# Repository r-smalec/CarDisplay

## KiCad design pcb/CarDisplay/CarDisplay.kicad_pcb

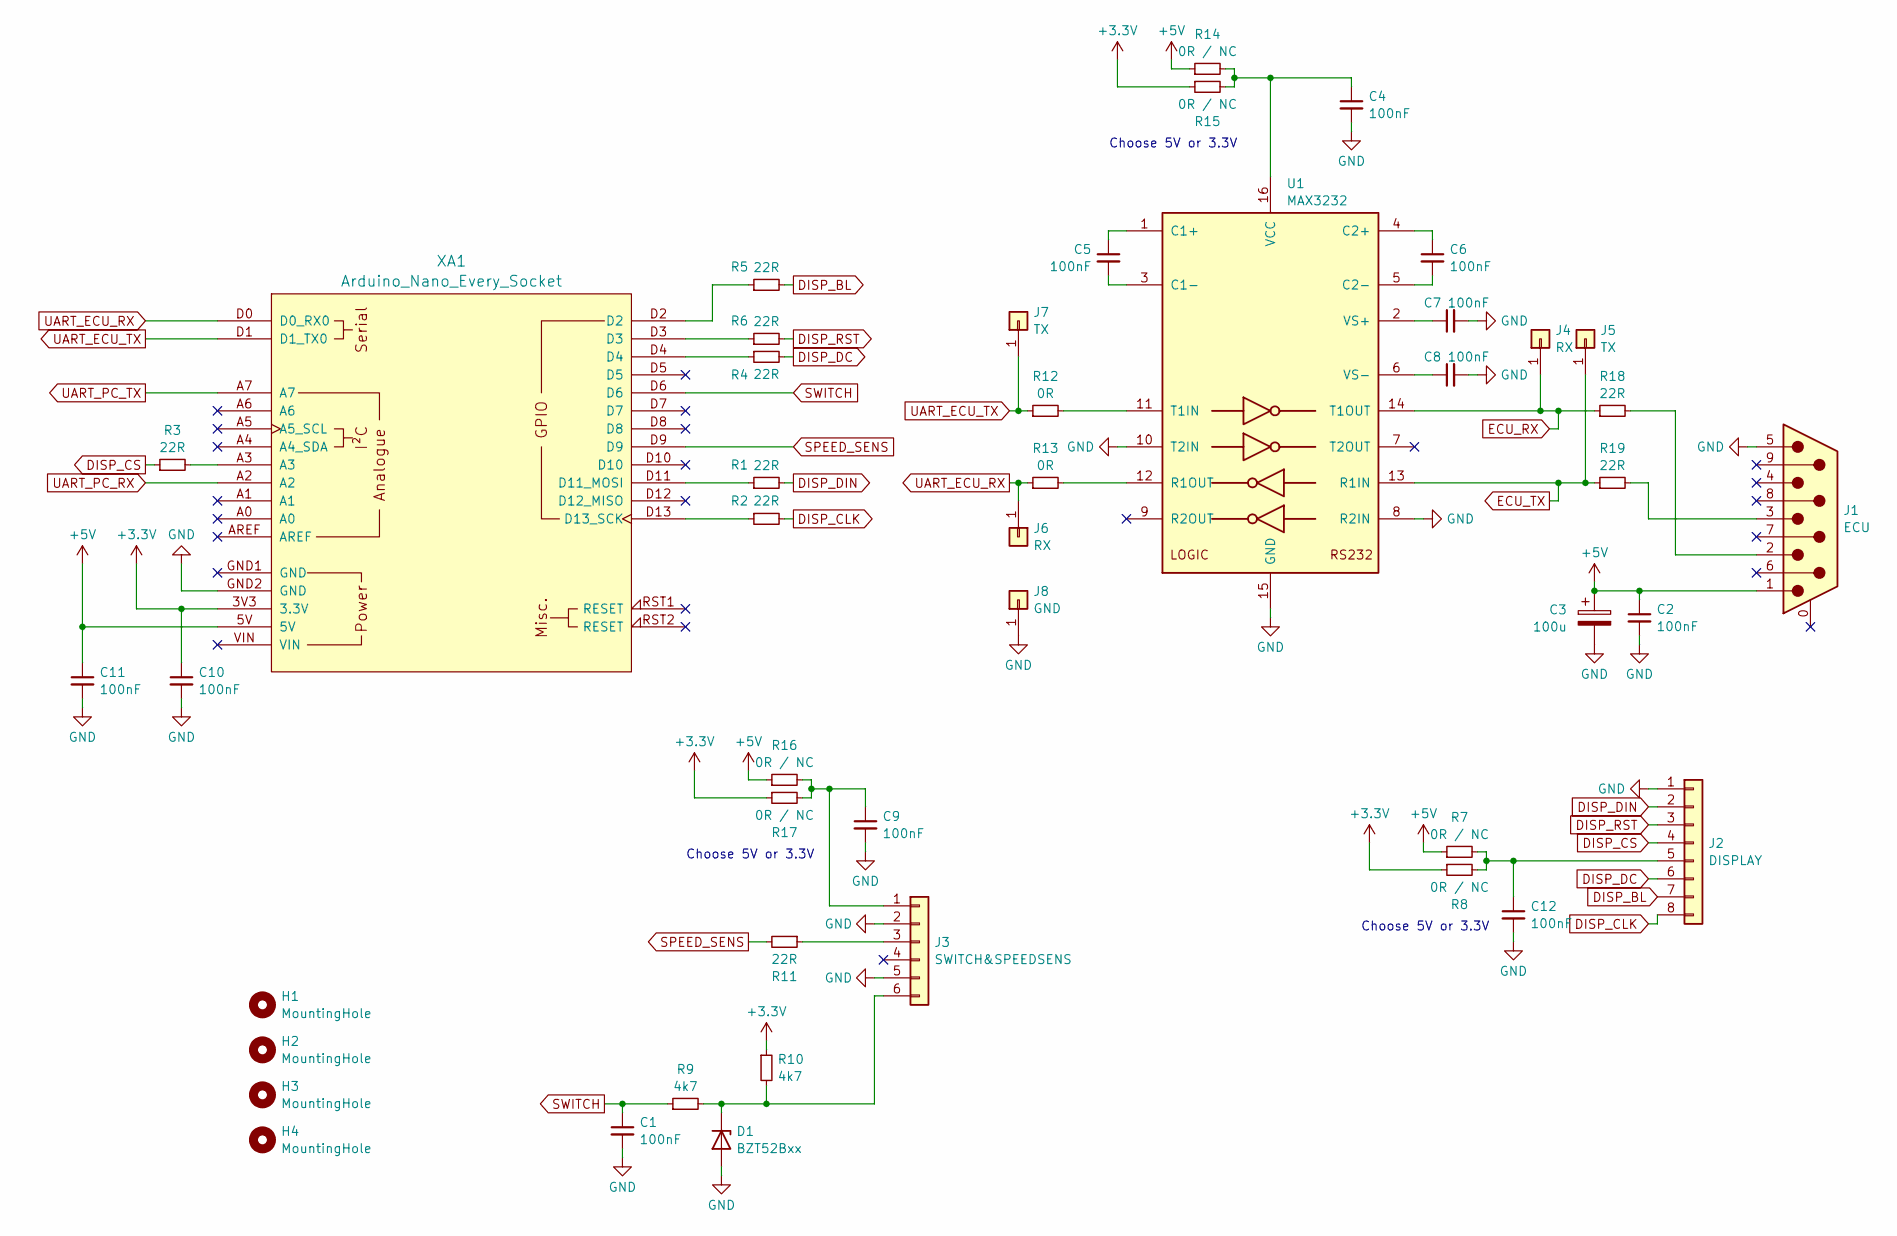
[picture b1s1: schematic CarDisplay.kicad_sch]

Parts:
C1, C2, C4, C5, C6, C7, C8, C9, C10, C11, C12: 100nF; C_1206_3216Metric_Pad1.33x1.80mm_HandSolder
C3: 100u; CP_LYING_16x10_5,0mm
D1: BZT52Bxx; D_SOD-123F
H1, H2, H3, H4: MountingHole; MountingHole_3.5mm
J1: ECU; DSUB-9_Female_Horizontal_P2.77x2.84mm_EdgePinOffset4.94mm_H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
J2: DISPLAY; Molex_Mini-Fit_Jr_5569-08A2_2x04_P4.20mm_Horizontal
J3: SWITCH&SPEEDSENS; Molex_Mini-Fit_Jr_5569-06A2_2x03_P4.20mm_Horizontal
J4, J6: RX; MeasuringPin
J5, J7: TX; MeasuringPin
J8: GND; MeasuringPin
R1, R2, R3, R4, R5, R6, R11, R18, R19: 22R; R_0805_2012Metric_Pad1.20x1.40mm_HandSolder
R7, R8, R14, R15, R16, R17: 0R / NC; R_0805_2012Metric_Pad1.20x1.40mm_HandSolder
R9, R10: 4k7; R_0805_2012Metric_Pad1.20x1.40mm_HandSolder
R12, R13: 0R; R_0805_2012Metric_Pad1.20x1.40mm_HandSolder
U1: MAX3232; SOIC-16_3.9x9.9mm_P1.27mm
XA1: Arduino_Nano_Every_Socket; Arduino_Nano_Socket

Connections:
+3.3V: C10.1, R8.1, R10.1, R15.1, R17.1, XA1.3V3 (3.3V)
+5V: C2.1, C3.1, C11.1, J1.1, R7.1, R14.1, R16.1, XA1.5V
DISP_BL: J2.7, R5.2
DISP_CLK: J2.8, R2.2
DISP_CS: J2.4, R3.1
DISP_DC: J2.6, R4.2
DISP_DIN: J2.2, R1.2
DISP_RST: J2.3, R6.2
ECU_RX: J4.1, R18.1, U1.14 (T1OUT)
ECU_TX: J5.1, R19.1, U1.13 (R1IN)
GND: C1.2, C2.2, C3.2, C4.2, C7.2, C8.2, C9.2, C10.2, C11.2, C12.2, D1.2 (A), J1.5, J2.1, J3.2, J3.5, J8.1, U1.8 (R2IN), U1.10 (T2IN), U1.15 (GND), XA1.GND2 (GND)
unnamed: D1.1 (K), J3.6, R9.2, R10.2
unnamed: J1.2, R18.2
unnamed: J1.3, R19.2
unnamed: C12.1, J2.5, R7.2, R8.2
unnamed: C9.1, J3.1, R16.2, R17.2
unnamed: J3.3, R11.1
unnamed: R3.2, XA1.A3
unnamed: R4.1, XA1.D4
unnamed: R5.1, XA1.D2
unnamed: R6.1, XA1.D3
unnamed: C5.1, U1.1 (C1+)
unnamed: C5.2, U1.3 (C1-)
unnamed: C6.1, U1.4 (C2+)
unnamed: C6.2, U1.5 (C2-)
unnamed: R13.2, U1.12 (R1OUT)
unnamed: R12.2, U1.11 (T1IN)
unnamed: C4.1, R14.2, R15.2, U1.16 (VCC)
unnamed: C7.1, U1.2 (VS+)
unnamed: C8.1, U1.6 (VS-)
unnamed: R1.1, XA1.D11 (D11_MOSI)
unnamed: R2.1, XA1.D13 (D13_SCK)
SPEED_SENS: R11.2, XA1.D9
SWITCH: C1.1, R9.1, XA1.D6
UART_ECU_RX: J6.1, R13.1, XA1.D0 (D0_RX0)
UART_ECU_TX: J7.1, R12.1, XA1.D1 (D1_TX0)
UART_PC_RX: XA1.A2
UART_PC_TX: XA1.A7

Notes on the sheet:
Choose 5V or 3.3V

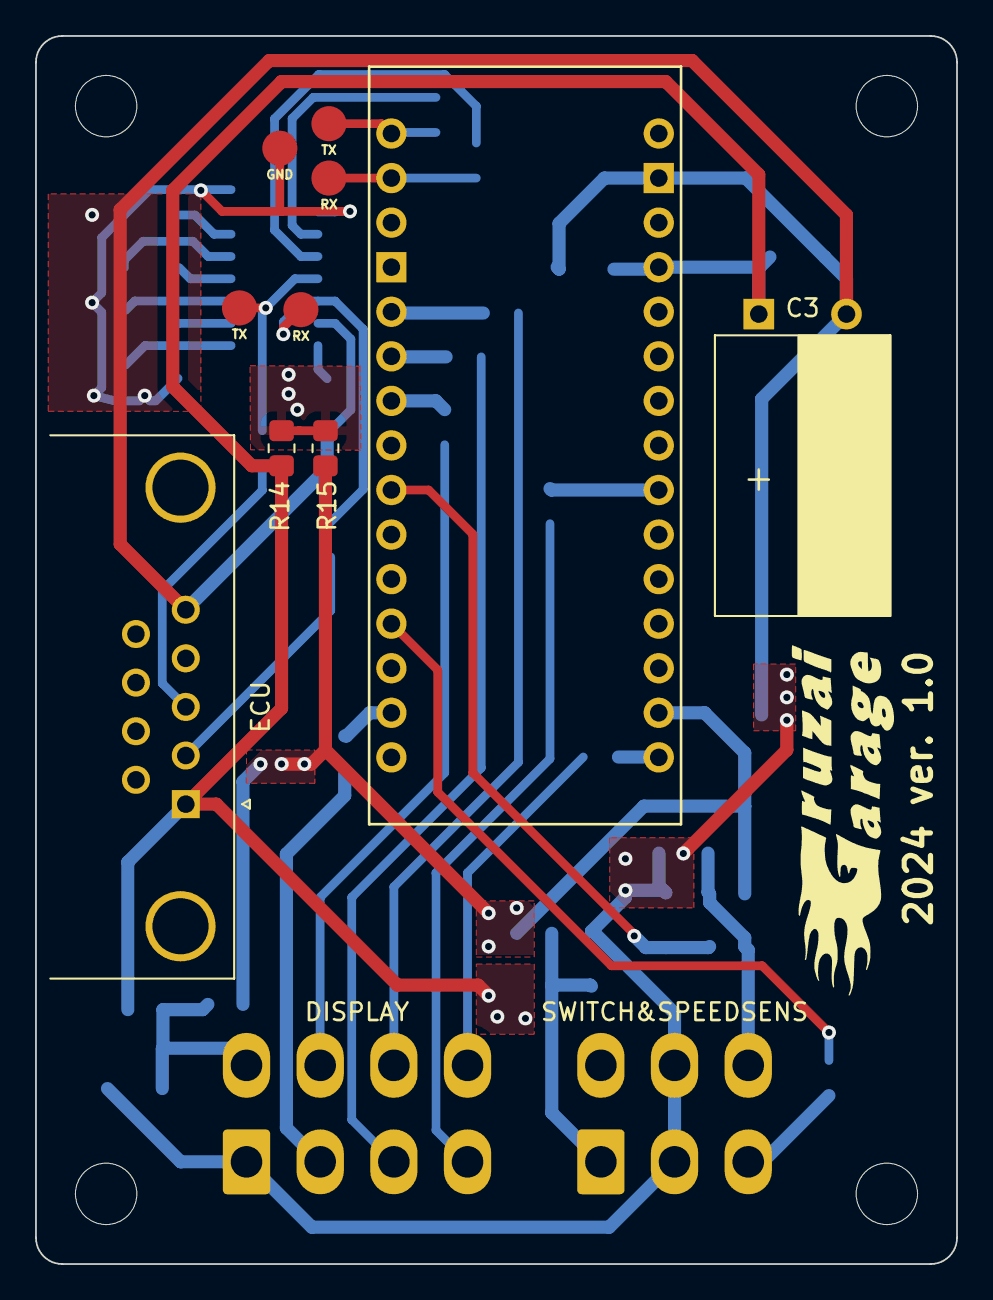
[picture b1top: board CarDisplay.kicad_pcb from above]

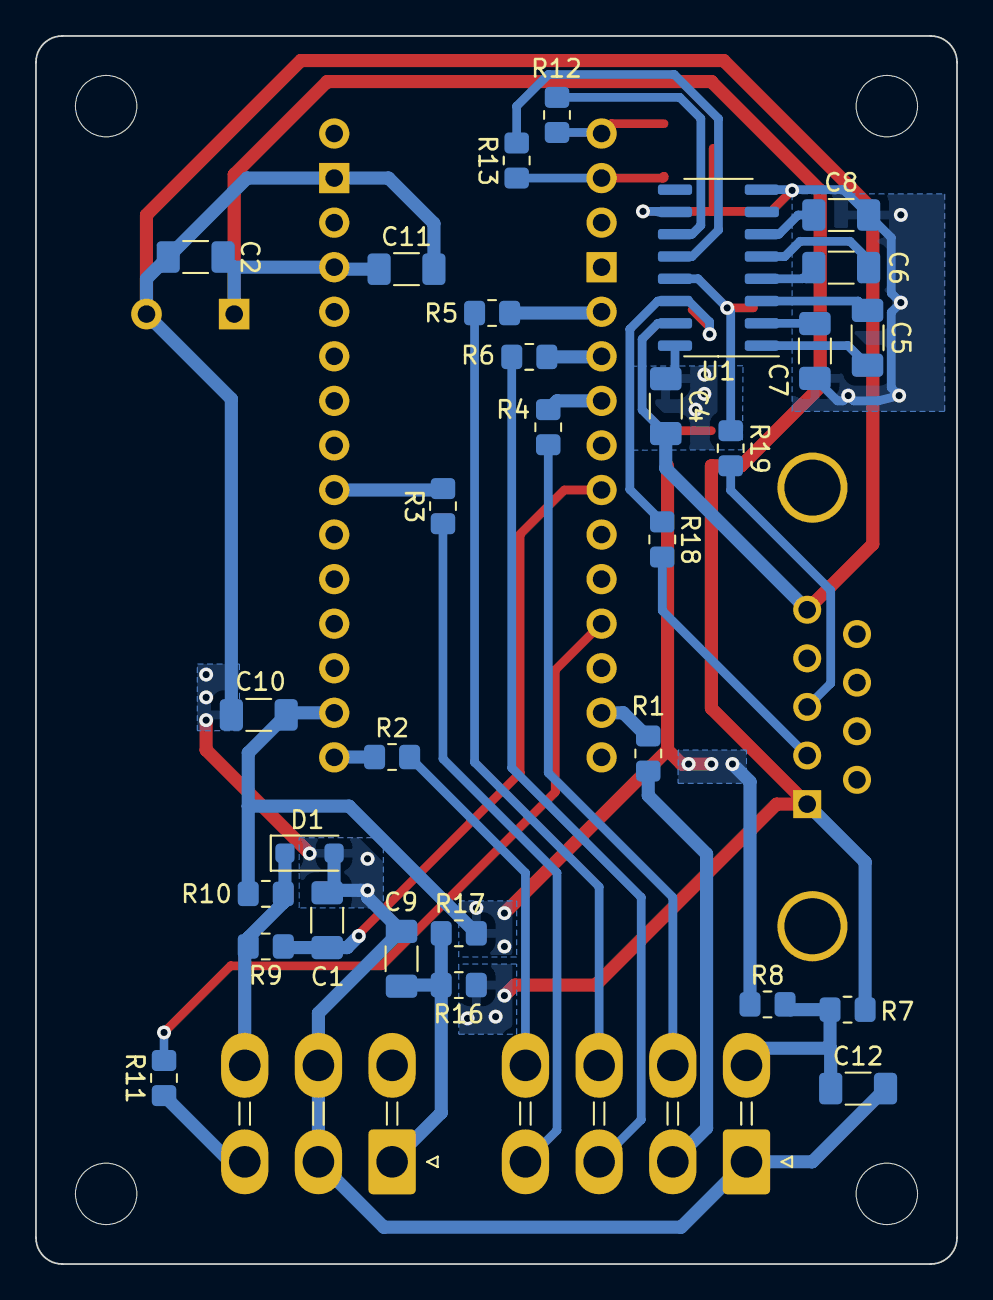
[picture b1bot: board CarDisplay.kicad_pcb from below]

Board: 2 copper layers, 52.5 x 70.0 mm, 46 parts (32 on the bottom side), 36 nets.

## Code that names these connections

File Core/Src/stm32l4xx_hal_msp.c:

/* USER CODE BEGIN Header */
/**
  ******************************************************************************
  * File Name          : stm32l4xx_hal_msp.c
  * Description        : This file provides code for the MSP Initialization 
  *                      and de-Initialization codes.
  ******************************************************************************
  * @attention
  *
  * <h2><center>&copy; Copyright (c) 2024 STMicroelectronics.
  * All rights reserved.</center></h2>
  *
  * This software component is licensed by ST under BSD 3-Clause license,
  * the "License"; You may not use this file except in compliance with the
  * License. You may obtain a copy of the License at:
  *                        opensource.org/licenses/BSD-3-Clause
  *
  ******************************************************************************
  */
/* USER CODE END Header */

/* Includes ------------------------------------------------------------------*/
#include "main.h"
/* USER CODE BEGIN Includes */

/* USER CODE END Includes */

/* Private typedef -----------------------------------------------------------*/
/* USER CODE BEGIN TD */

/* USER CODE END TD */

/* Private define ------------------------------------------------------------*/
/* USER CODE BEGIN Define */
 
/* USER CODE END Define */

/* Private macro -------------------------------------------------------------*/
/* USER CODE BEGIN Macro */

/* USER CODE END Macro */

/* Private variables ---------------------------------------------------------*/
/* USER CODE BEGIN PV */

/* USER CODE END PV */

/* Private function prototypes -----------------------------------------------*/
/* USER CODE BEGIN PFP */

/* USER CODE END PFP */

/* External functions --------------------------------------------------------*/
/* USER CODE BEGIN ExternalFunctions */

/* USER CODE END ExternalFunctions */

/* USER CODE BEGIN 0 */

/* USER CODE END 0 */
/**
  * Initializes the Global MSP.
  */
void HAL_MspInit(void)
{
  /* USER CODE BEGIN MspInit 0 */

  /* USER CODE END MspInit 0 */

  __HAL_RCC_SYSCFG_CLK_ENABLE();
  __HAL_RCC_PWR_CLK_ENABLE();

  /* System interrupt init*/

  /* USER CODE BEGIN MspInit 1 */

  /* USER CODE END MspInit 1 */
}

/**
* @brief SPI MSP Initialization
* This function configures the hardware resources used in this example
* @param hspi: SPI handle pointer
* @retval None
*/
void HAL_SPI_MspInit(SPI_HandleTypeDef* hspi)
{
  GPIO_InitTypeDef GPIO_InitStruct = {0};
  if(hspi->Instance==SPI1)
  {
  /* USER CODE BEGIN SPI1_MspInit 0 */

  /* USER CODE END SPI1_MspInit 0 */
    /* Peripheral clock enable */
    __HAL_RCC_SPI1_CLK_ENABLE();
  
    __HAL_RCC_GPIOA_CLK_ENABLE();
    /**SPI1 GPIO Configuration    
    PA4     ------> SPI1_NSS
    PA5     ------> SPI1_SCK
    PA7     ------> SPI1_MOSI 
    */
    GPIO_InitStruct.Pin = DISP_CS_Pin|DISP_CLK_Pin|DISP_DIN_Pin;
    GPIO_InitStruct.Mode = GPIO_MODE_AF_PP;
    GPIO_InitStruct.Pull = GPIO_NOPULL;
    GPIO_InitStruct.Speed = GPIO_SPEED_FREQ_VERY_HIGH;
    GPIO_InitStruct.Alternate = GPIO_AF5_SPI1;
    HAL_GPIO_Init(GPIOA, &GPIO_InitStruct);

  /* USER CODE BEGIN SPI1_MspInit 1 */

  /* USER CODE END SPI1_MspInit 1 */
  }

}

/**
* @brief SPI MSP De-Initialization
* This function freeze the hardware resources used in this example
* @param hspi: SPI handle pointer
* @retval None
*/
void HAL_SPI_MspDeInit(SPI_HandleTypeDef* hspi)
{
  if(hspi->Instance==SPI1)
  {
  /* USER CODE BEGIN SPI1_MspDeInit 0 */

  /* USER CODE END SPI1_MspDeInit 0 */
    /* Peripheral clock disable */
    __HAL_RCC_SPI1_CLK_DISABLE();
  
    /**SPI1 GPIO Configuration    
    PA4     ------> SPI1_NSS
    PA5     ------> SPI1_SCK
    PA7     ------> SPI1_MOSI 
    */
    HAL_GPIO_DeInit(GPIOA, DISP_CS_Pin|DISP_CLK_Pin|DISP_DIN_Pin);

  /* USER CODE BEGIN SPI1_MspDeInit 1 */

  /* USER CODE END SPI1_MspDeInit 1 */
  }

}

/**
* @brief TIM_IC MSP Initialization
* This function configures the hardware resources used in this example
* @param htim_ic: TIM_IC handle pointer
* @retval None
*/
void HAL_TIM_IC_MspInit(TIM_HandleTypeDef* htim_ic)
{
  GPIO_InitTypeDef GPIO_InitStruct = {0};
  if(htim_ic->Instance==TIM1)
  {
  /* USER CODE BEGIN TIM1_MspInit 0 */

  /* USER CODE END TIM1_MspInit 0 */
    /* Peripheral clock enable */
    __HAL_RCC_TIM1_CLK_ENABLE();
  
    __HAL_RCC_GPIOA_CLK_ENABLE();
    /**TIM1 GPIO Configuration    
    PA8     ------> TIM1_CH1 
    */
    GPIO_InitStruct.Pin = SPEED_SENS_Pin;
    GPIO_InitStruct.Mode = GPIO_MODE_AF_PP;
    GPIO_InitStruct.Pull = GPIO_NOPULL;
    GPIO_InitStruct.Speed = GPIO_SPEED_FREQ_LOW;
    GPIO_InitStruct.Alternate = GPIO_AF1_TIM1;
    HAL_GPIO_Init(SPEED_SENS_GPIO_Port, &GPIO_InitStruct);

  /* USER CODE BEGIN TIM1_MspInit 1 */

  /* USER CODE END TIM1_MspInit 1 */
  }

}

/**
* @brief TIM_IC MSP De-Initialization
* This function freeze the hardware resources used in this example
* @param htim_ic: TIM_IC handle pointer
* @retval None
*/
void HAL_TIM_IC_MspDeInit(TIM_HandleTypeDef* htim_ic)
{
  if(htim_ic->Instance==TIM1)
  {
  /* USER CODE BEGIN TIM1_MspDeInit 0 */

  /* USER CODE END TIM1_MspDeInit 0 */
    /* Peripheral clock disable */
    __HAL_RCC_TIM1_CLK_DISABLE();
  
    /**TIM1 GPIO Configuration    
    PA8     ------> TIM1_CH1 
    */
    HAL_GPIO_DeInit(SPEED_SENS_GPIO_Port, SPEED_SENS_Pin);

  /* USER CODE BEGIN TIM1_MspDeInit 1 */

  /* USER CODE END TIM1_MspDeInit 1 */
  }

}

/**
* @brief UART MSP Initialization
* This function configures the hardware resources used in this example
* @param huart: UART handle pointer
* @retval None
*/
void HAL_UART_MspInit(UART_HandleTypeDef* huart)
{
  GPIO_InitTypeDef GPIO_InitStruct = {0};
  if(huart->Instance==USART1)
  {
  /* USER CODE BEGIN USART1_MspInit 0 */

  /* USER CODE END USART1_MspInit 0 */
    /* Peripheral clock enable */
    __HAL_RCC_USART1_CLK_ENABLE();
  
    __HAL_RCC_GPIOA_CLK_ENABLE();
    /**USART1 GPIO Configuration    
    PA9     ------> USART1_TX
    PA10     ------> USART1_RX 
    */
    GPIO_InitStruct.Pin = UART_ECU_TX_Pin|UART_ECU_RX_Pin;
    GPIO_InitStruct.Mode = GPIO_MODE_AF_PP;
    GPIO_InitStruct.Pull = GPIO_NOPULL;
    GPIO_InitStruct.Speed = GPIO_SPEED_FREQ_VERY_HIGH;
    GPIO_InitStruct.Alternate = GPIO_AF7_USART1;
    HAL_GPIO_Init(GPIOA, &GPIO_InitStruct);

  /* USER CODE BEGIN USART1_MspInit 1 */

  /* USER CODE END USART1_MspInit 1 */
  }
  else if(huart->Instance==USART2)
  {
  /* USER CODE BEGIN USART2_MspInit 0 */

  /* USER CODE END USART2_MspInit 0 */
    /* Peripheral clock enable */
    __HAL_RCC_USART2_CLK_ENABLE();
  
    __HAL_RCC_GPIOA_CLK_ENABLE();
    /**USART2 GPIO Configuration    
    PA2     ------> USART2_TX
    PA3     ------> USART2_RX 
    */
    GPIO_InitStruct.Pin = UART_PC_TX_Pin|UART_PC_RX_Pin;
    GPIO_InitStruct.Mode = GPIO_MODE_AF_PP;
    GPIO_InitStruct.Pull = GPIO_NOPULL;
    GPIO_InitStruct.Speed = GPIO_SPEED_FREQ_VERY_HIGH;
    GPIO_InitStruct.Alternate = GPIO_AF7_USART2;
    HAL_GPIO_Init(GPIOA, &GPIO_InitStruct);

  /* USER CODE BEGIN USART2_MspInit 1 */

  /* USER CODE END USART2_MspInit 1 */
  }

}

/**
* @brief UART MSP De-Initialization
* This function freeze the hardware resources used in this example
* @param huart: UART handle pointer
* @retval None
*/
void HAL_UART_MspDeInit(UART_HandleTypeDef* huart)
{
  if(huart->Instance==USART1)
  {
  /* USER CODE BEGIN USART1_MspDeInit 0 */

  /* USER CODE END USART1_MspDeInit 0 */
    /* Peripheral clock disable */
    __HAL_RCC_USART1_CLK_DISABLE();
  
    /**USART1 GPIO Configuration    
    PA9     ------> USART1_TX
    PA10     ------> USART1_RX 
    */
    HAL_GPIO_DeInit(GPIOA, UART_ECU_TX_Pin|UART_ECU_RX_Pin);

  /* USER CODE BEGIN USART1_MspDeInit 1 */

  /* USER CODE END USART1_MspDeInit 1 */
  }
  else if(huart->Instance==USART2)
  {
  /* USER CODE BEGIN USART2_MspDeInit 0 */

  /* USER CODE END USART2_MspDeInit 0 */
    /* Peripheral clock disable */
    __HAL_RCC_USART2_CLK_DISABLE();
  
    /**USART2 GPIO Configuration    
    PA2     ------> USART2_TX
    PA3     ------> USART2_RX 
    */
    HAL_GPIO_DeInit(GPIOA, UART_PC_TX_Pin|UART_PC_RX_Pin);

  /* USER CODE BEGIN USART2_MspDeInit 1 */

  /* USER CODE END USART2_MspDeInit 1 */
  }

}

/* USER CODE BEGIN 1 */

/* USER CODE END 1 */

/************************ (C) COPYRIGHT STMicroelectronics *****END OF FILE****/

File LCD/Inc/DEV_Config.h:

#ifndef _DEV_CONFIG_H_
#define _DEV_CONFIG_H_

#include <stdint.h>
#include <stdio.h>
#include <stdlib.h>		//itoa()
#include "Debug.h"
#include "main.h"

#define DEV_RST_PIN     	DISP_RST_GPIO_Port, DISP_RST_Pin
#define DEV_DC_PIN      	DISP_DC_GPIO_Port, DISP_DC_Pin
#define DEV_CS_PIN			DISP_CS_GPIO_Port, DISP_CS_Pin
#define DEV_BL_PIN			DISP_BL_GPIO_Port, DISP_BL_Pin

SPI_HandleTypeDef *_hspi;


#define DISP_HEIGHT 240
#define DISP_WIDTH 240

#define HORIZONTAL 0
#define VERTICAL   1

void DISP_Init(SPI_HandleTypeDef *hspi, uint8_t Scan_dir);
void DISP_Exit(void);
void DISP_Reset(void);
void DISP_SendCommand(uint8_t reg);
void DISP_SendData_8Bit(uint8_t data);
void DISP_SendData_16Bit(uint16_t data);

void DISP_Clear(uint16_t Color);
void DISP_Display(uint16_t *Image);
void DISP_DisplayWindows(uint16_t Xstart, uint16_t Ystart, uint16_t Xend, uint16_t Yend, uint16_t *Image);
void DISP_DisplayPoint(uint16_t X, uint16_t Y, uint16_t Color);

void DISP_DrawPaint(uint16_t x, uint16_t y, uint16_t Color);
void DISP_SetBackLight(uint8_t Value);

#endif

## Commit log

2024-02-02 Intial commit
2024-02-02 Added lib to control lcd disp
2024-02-02 LCD library cleanup
2024-02-02 LCD lib cleanup
2024-02-11 display shows image
2024-02-11 display background cleared
2024-02-13 Table with parameters added to dispaly
2024-02-13 gearbox display added
2024-02-15 structure changed, pcb added
2024-02-15 gitignore updated
2024-02-16 pcb dev
2024-02-17 pcb dev, looking for better connectors
2024-02-17 firmware changed location, tim2 and exti added
2024-02-20 proper menu change
2024-02-28 readme
2024-02-28 pcb finished
2024-02-28 drc passed
2024-03-20 Emu Serial lib added
2024-03-20 Arduino exampl code added
2024-03-20 batt voltage display fix
2025-05-04 changed position of elements on the display
